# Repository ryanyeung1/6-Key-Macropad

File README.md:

# 8-Key-Macropad
PCB and Case for a small 8 key macropad

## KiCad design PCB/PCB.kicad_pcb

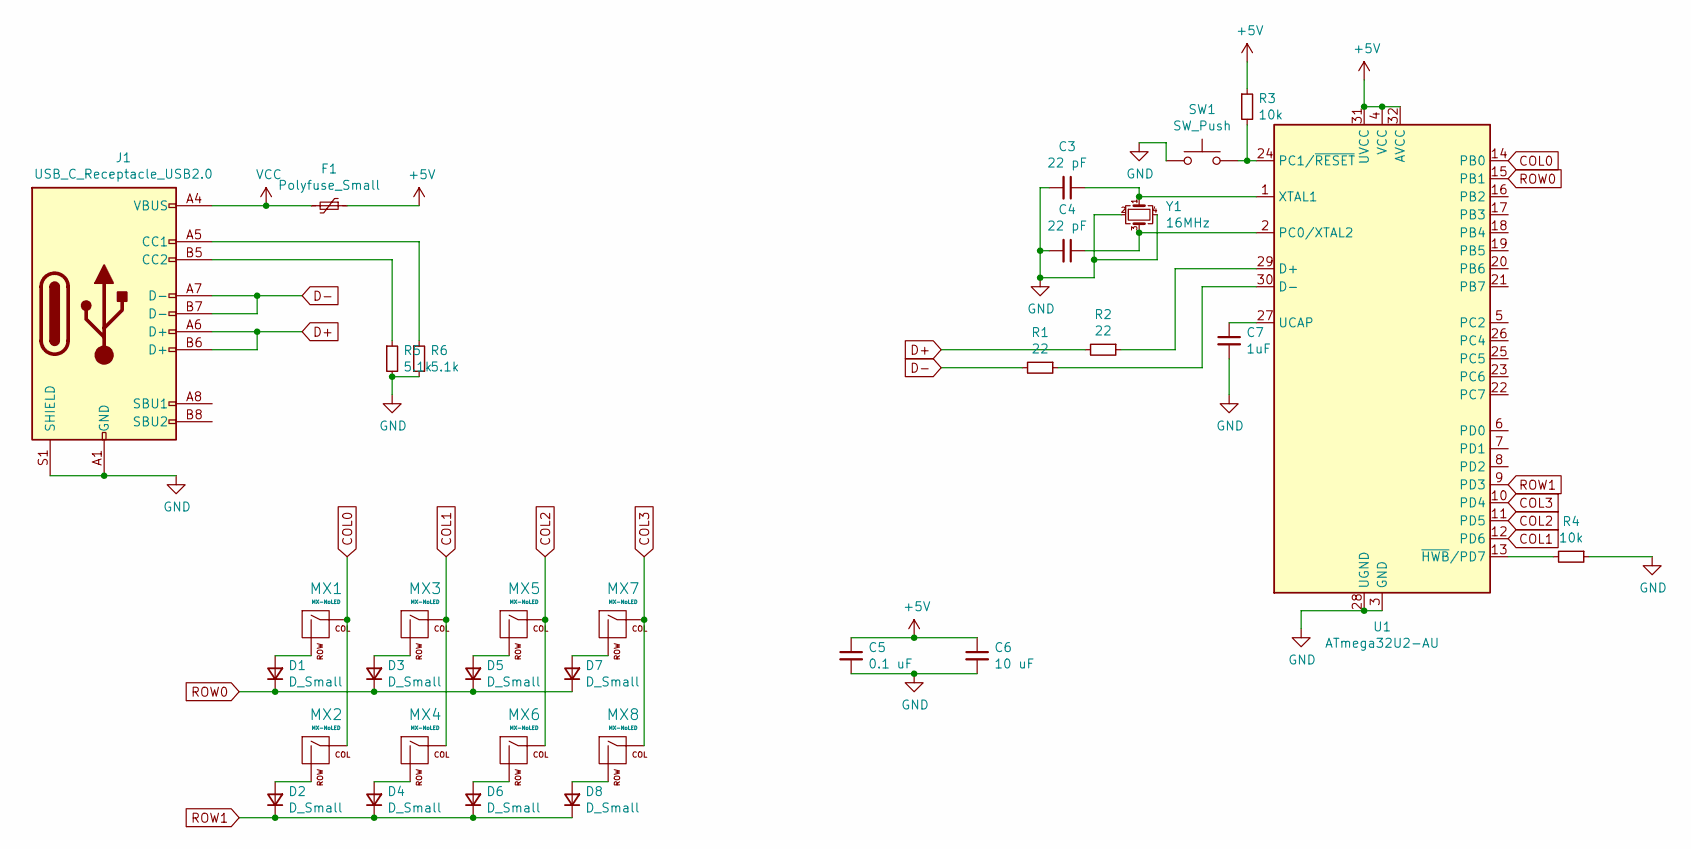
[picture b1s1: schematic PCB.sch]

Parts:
C3, C4: 22 pF; C_0805_2012Metric
C5: 0.1 uF; C_0805_2012Metric
C6: 10 uF; C_0805_2012Metric
C7: 1uF; C_0805_2012Metric
D1, D2, D3, D4, D5, D6, D7, D8: D_Small; D_SOD-123
F1: Polyfuse_Small; Fuse_1206_3216Metric
J1: USB_C_Receptacle_USB2.0; USB_C_Receptacle_GCT_USB4085
MX1, MX2, MX3, MX4, MX5, MX6, MX7, MX8: MX-NoLED; MX-1U-NoLED
R1, R2: 22; R_0805_2012Metric
R3, R4: 10k; R_0805_2012Metric
R5, R6: 5.1k; R_0805_2012Metric
SW1: SW_Push; SKQG-1155865
U1: ATmega32U2-AU; TQFP-32_7x7mm_P0.8mm
Y1: 16MHz; Crystal_SMD_3225-4Pin_3.2x2.5mm

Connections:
+5V: C5.1, C6.1, F1.1, R3.1, U1.4 (VCC), U1.31 (UVCC), U1.32 (AVCC)
COL0: MX1.1 (COL), MX2.1 (COL), U1.14 (PB0)
COL1: MX3.1 (COL), MX4.1 (COL), U1.12 (PD6)
COL2: MX5.1 (COL), MX6.1 (COL), U1.11 (PD5)
COL3: MX7.1 (COL), MX8.1 (COL), U1.10 (PD4)
D+: J1.A6 (D+), J1.B6 (D+), R2.2
D-: J1.A7 (D-), J1.B7 (D-), R1.2
GND: C3.2, C4.2, C5.2, C6.2, C7.2, J1.A1 (GND), J1.A12 (GND), J1.B1 (GND), J1.B12 (GND), J1.S1 (SHIELD), R4.1, R5.2, R6.2, SW1.1, U1.3 (GND), U1.28 (UGND), Y1.2, Y1.4
unnamed: C3.1, U1.1 (XTAL1), Y1.1
unnamed: C4.1, U1.2 (PC0/XTAL2), Y1.3
unnamed: C7.1, U1.27 (UCAP)
unnamed: D1.2 (A), MX1.2 (ROW)
unnamed: D2.2 (A), MX2.2 (ROW)
unnamed: D3.2 (A), MX3.2 (ROW)
unnamed: D4.2 (A), MX4.2 (ROW)
unnamed: D5.2 (A), MX5.2 (ROW)
unnamed: D6.2 (A), MX6.2 (ROW)
unnamed: D7.2 (A), MX7.2 (ROW)
unnamed: D8.2 (A), MX8.2 (ROW)
unnamed: J1.A5 (CC1), R6.1
unnamed: J1.B5 (CC2), R5.1
unnamed: R1.1, U1.30 (D-)
unnamed: R2.1, U1.29 (D+)
unnamed: R3.2, SW1.2, U1.24 (PC1/~RESET)
unnamed: R4.2, U1.13 (~HWB~/PD7)
ROW0: D1.1 (K), D3.1 (K), D5.1 (K), D7.1 (K), U1.15 (PB1)
ROW1: D2.1 (K), D4.1 (K), D6.1 (K), D8.1 (K), U1.9 (PD3)
VCC: F1.2, J1.A4 (VBUS), J1.A9 (VBUS), J1.B4 (VBUS), J1.B9 (VBUS)

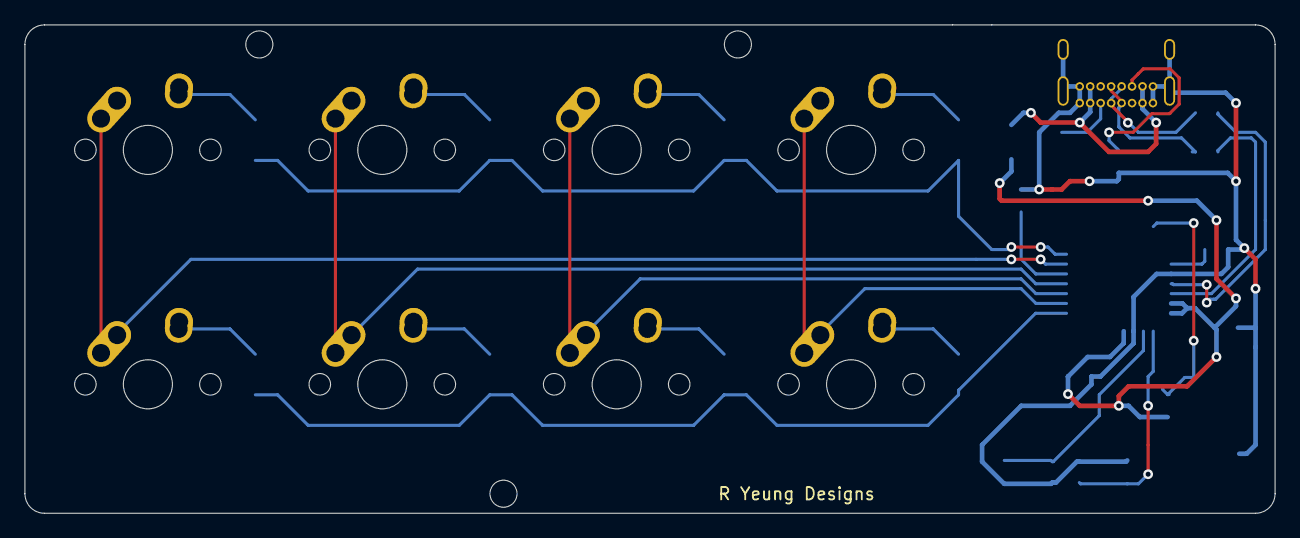
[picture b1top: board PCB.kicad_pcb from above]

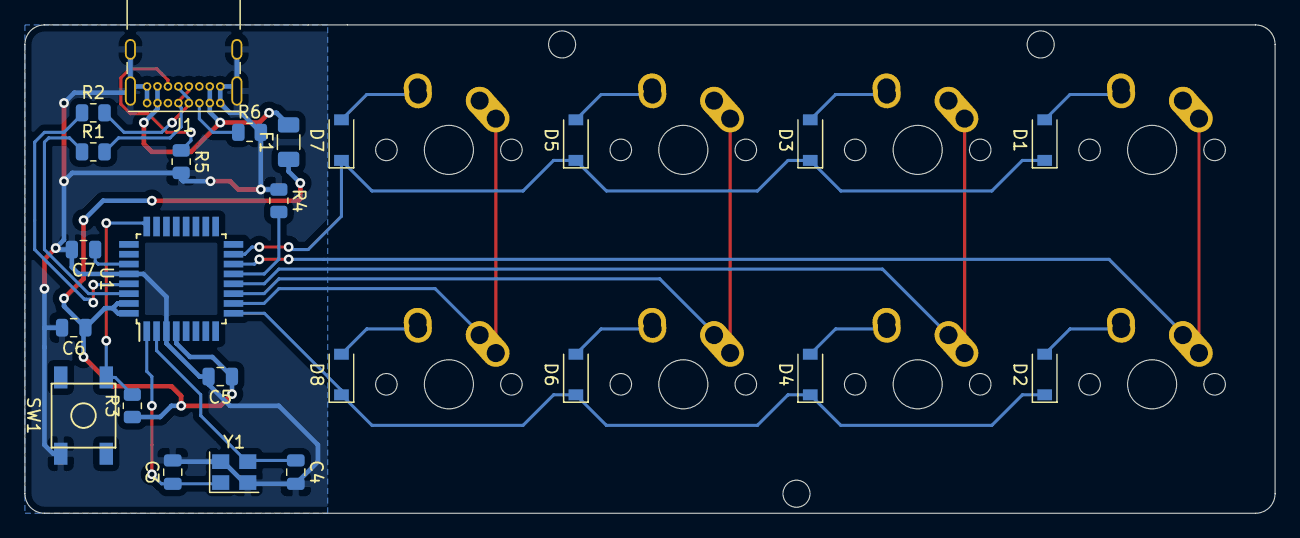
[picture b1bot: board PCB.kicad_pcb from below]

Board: 2 copper layers, 101.6 x 39.7 mm, 32 parts (24 on the bottom side), 28 nets.

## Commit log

2021-05-01 created_PCB_files
2021-05-01 add submodules
2021-05-01 added libraries
2021-05-01 first part schematic
2021-05-01 finished schematics and assigned footprints
2021-05-02 routed PCB
2021-05-02 finished PCB?
2021-05-02 added through-holes
2021-05-02 rerouted usb to make more parallel
2021-05-02 major changes: replaced usb with usb type C
2021-05-02 replaced usb footprint with GCT-usb4085 available in digikey
2021-05-06 added case and updated usb-c footprint
2021-05-06 small case edits and created STL files
2021-05-07 replaced mc with ATMEGA32u2
2021-05-07 generated gerber files
2021-05-22 added firmware
2021-05-30 added numbers.hex
2021-06-26 small case changes
2021-11-04 removed silkscreen
